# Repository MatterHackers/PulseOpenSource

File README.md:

Pulse 3D Printers
=================

The [Pulse](https://www.matterhackers.com/pulse) is a customizable built-to-order 3D printer produced by
[MatterHackers](https://www.matterhackers.com/). The Pulse is based on the Prusa i3. This repository contains the source code
and design files.

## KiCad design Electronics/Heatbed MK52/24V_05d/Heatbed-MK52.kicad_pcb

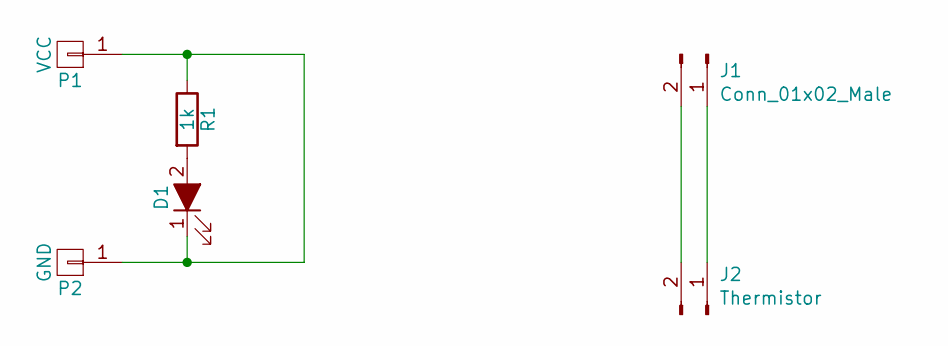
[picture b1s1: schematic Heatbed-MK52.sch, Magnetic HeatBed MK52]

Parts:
D1: LED_ALT; LED_0805
J1: Conn_01x02_Male; Molex_Micro-Fit_3.0_43650-0200_1x02_P3.00mm_Horizontal
J2: Thermistor
P1: VCC; PCB-Large-pad
P2: GND; PCB-Large-pad
R1: 1k; R_0805_HandSoldering

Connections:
unnamed: D1.1 (K), P1.1, P2.1, R1.1
unnamed: D1.2 (A), R1.2
unnamed: J1.1, J2.1
unnamed: J1.2, J2.2

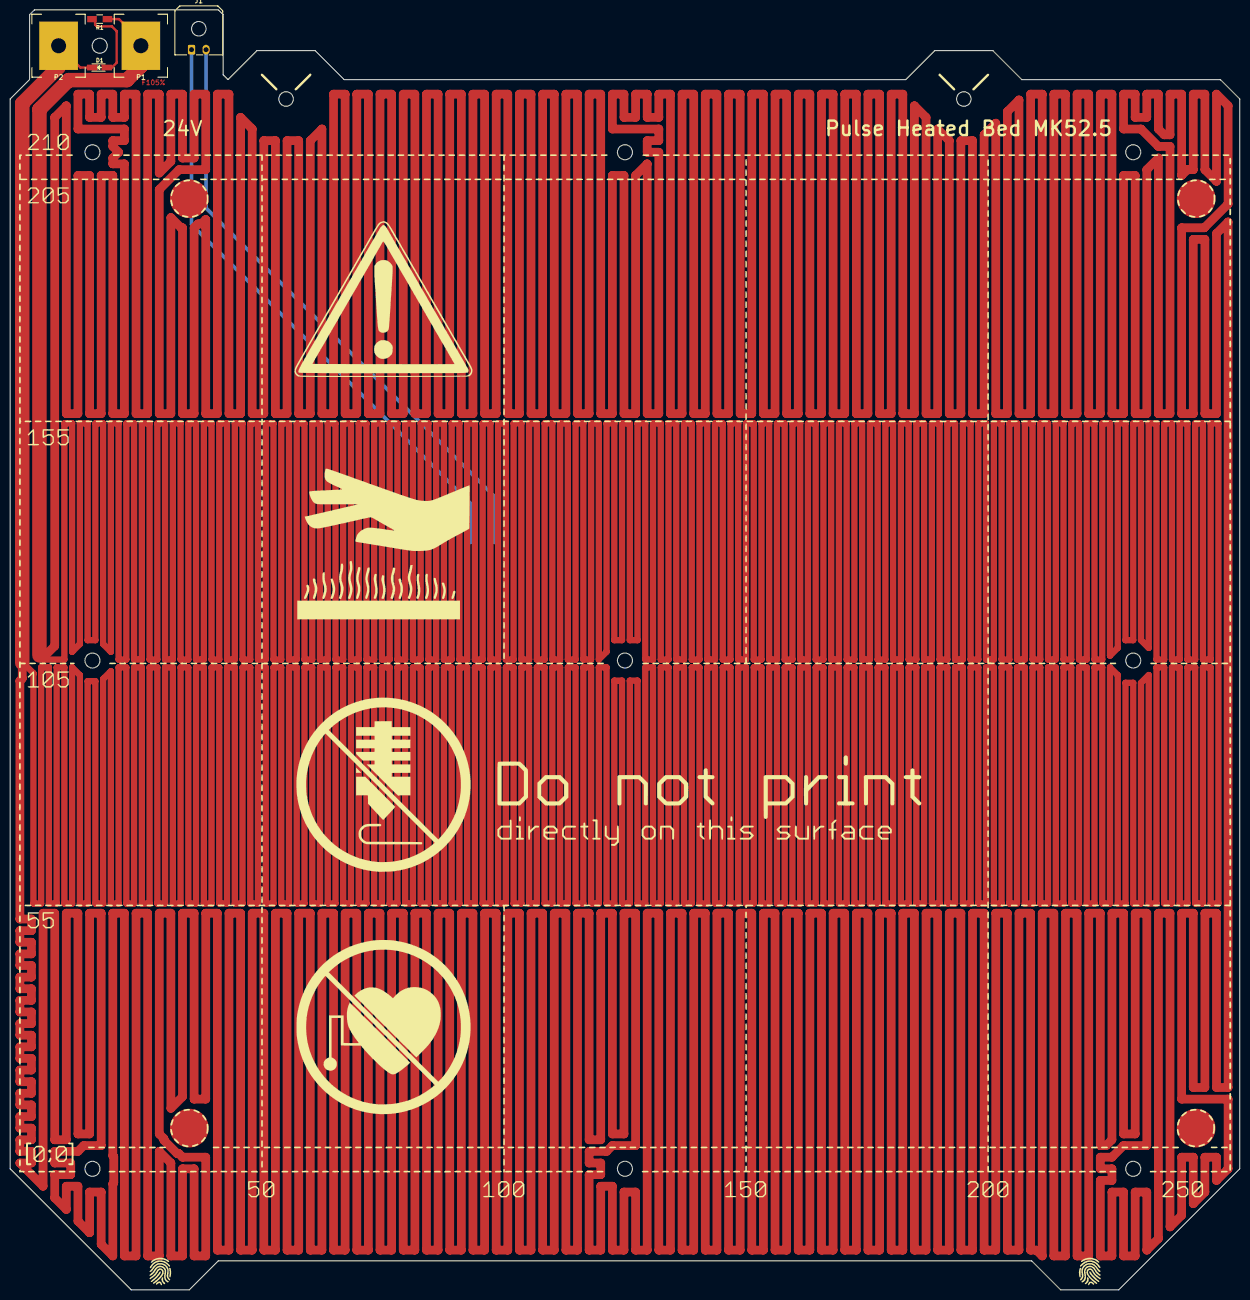
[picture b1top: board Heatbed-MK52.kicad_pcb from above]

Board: 2 copper layers, 254.0 x 264.4 mm, 6 parts (1 on the bottom side), 4 nets.

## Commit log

2019-07-02 updated STL files for Hot End
2020-02-12 Updated D frame files and added DXE
2020-08-01 adding thumbnail image
2020-08-31 Added E Series (v5.0.0) parts
2020-09-03 putting in image thumbnails
2020-09-04 Rotated STLs for printing
2020-09-04 Rotated y belt holder
2020-09-04 rotated parts renders
2020-09-10 Put in DXE
2020-09-21 Renamed and copied old hot end parts which are still in use
2020-09-28 Adding in clip
2020-09-28 put in images
2020-09-28 Adding accessories
2020-10-10 Added Mosquito parts
2020-10-13 Fixed 706 Extrusion Wire Clamp
2020-10-13 Better snap fit on Rambo box lid
2020-10-13 Added Volcano parts
2020-10-14 Standardize hot end wire covers
2020-10-14 Added Lite6 fan shroud for 40mm fans
2020-10-14 Slimmed down bed wire cover
2020-10-17 Added 40mm Mosquito fan shroud
2020-10-17 Removed hex holes from PSU case
2020-10-17 Added EZR frame mount
2020-11-16 Improved fit on groove heat sink mount
2020-11-18 Chamfered 105 Y Belt Holder
2020-11-20 Tapered belt slots in X carriage
2021-02-04 Adjustments to improve print quality of some parts
2021-02-04 Elongated screw holes in PSU top
2021-04-05 Switch Y endstop mount to 2mm screws
2021-04-05 Seperated E Series DXE parts
2021-04-05 Widened gap for wires in PSU parts
2021-04-08 Extended stop on Y belt holder
2021-04-19 HotSwap system
2021-04-19 New DXE motherboard box
2021-04-19 Upload STEP files for most parts
2021-04-19 Upload electronics designs and wiring diagrams
2021-04-25 moving images into sub folders
2021-04-27 Add new images
2021-05-14 Elongated holes in PSU top
2023-01-03 new snap hotend mounts
2023-01-24 adding 410 orbiter extruder
2023-10-11 adding fysetc lcd mount
2023-10-11 removed dovetail parts.
2023-12-26 Adding wide wire cover
2023-12-26 uploading new images
2024-02-08 Adding SKR Turbo case and lid
